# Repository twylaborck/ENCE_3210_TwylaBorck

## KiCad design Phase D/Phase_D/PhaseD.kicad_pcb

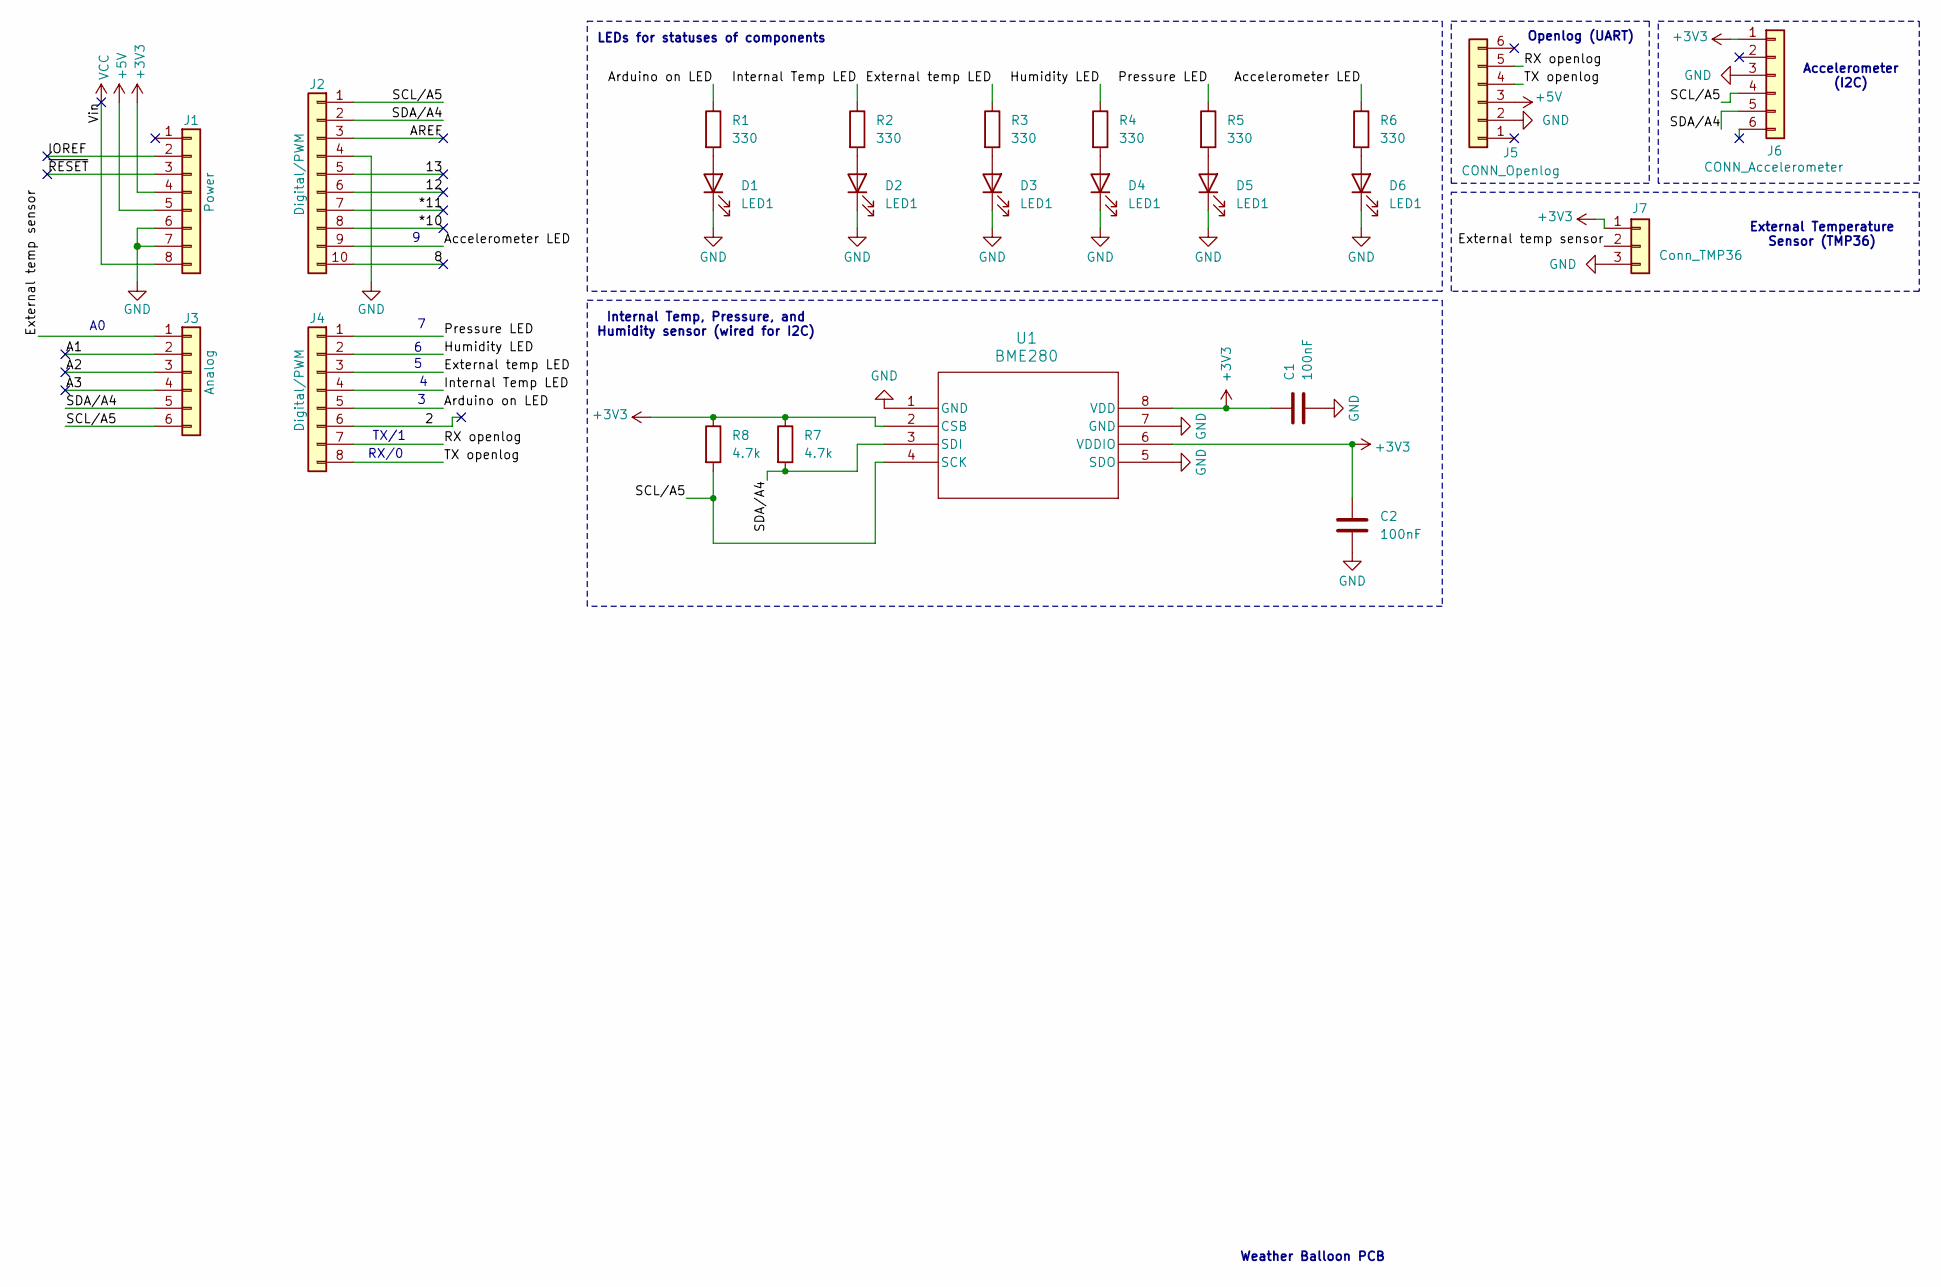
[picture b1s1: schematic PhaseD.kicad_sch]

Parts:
C1, C2: 100nF; C_Disc_D5.0mm_W2.5mm_P5.00mm
D1, D2, D3, D4, D5, D6: LED1; LED_D5.0mm
J1: Power; PinSocket_1x08_P2.54mm_Vertical
J2: Digital/PWM; PinSocket_1x10_P2.54mm_Vertical
J3: Analog; PinSocket_1x06_P2.54mm_Vertical
J4: Digital/PWM; PinSocket_1x08_P2.54mm_Vertical
J5: CONN_Openlog; PinHeader_1x06_P2.54mm_Vertical
J6: CONN_Accelerometer; PinHeader_1x06_P2.54mm_Vertical
J7: Conn_TMP36; PinHeader_1x03_P2.00mm_Vertical
R1, R2, R3, R4, R5, R6: 330; R_Axial_DIN0207_L6.3mm_D2.5mm_P10.16mm_Horizontal
R7, R8: 4.7k; R_Axial_DIN0207_L6.3mm_D2.5mm_P10.16mm_Horizontal
U1: BME280; DFN8_0p65_2p5SQ_BOS

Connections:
+3V3: C1.1, C2.1, J1.4, J6.1, J7.1, R7.1, R8.1, U1.2 (CSB), U1.6 (VDDIO), U1.8 (VDD)
+5V: J1.5, J5.3
/2: J4.6
/8: J2.10
/12: J2.6
/13: J2.5
/*10: J2.8
/*11: J2.7
/A1: J3.2
/A2: J3.3
/A3: J3.4
/AREF: J2.3
/Accelerometer LED: J2.9, R6.1
/Arduino on LED: J4.5, R1.1
/External temp LED: J4.3, R3.1
/External temp sensor: J3.1, J7.2
/Humidity LED: J4.2, R4.1
/IOREF: J1.2
/Internal Temp LED: J4.4, R2.1
/Pressure LED: J4.1, R5.1
/RX openlog: J4.7, J5.5
/SCL/A5: J2.1, J3.6, J6.4, R8.2, U1.4 (SCK)
/SDA/A4: J2.2, J3.5, J6.5, R7.2, U1.3 (SDI)
/TX openlog: J4.8, J5.4
/~RESET: J1.3
GND: C1.2, C2.2, D1.1 (K), D2.1 (K), D3.1 (K), D4.1 (K), D5.1 (K), D6.1 (K), J1.6, J1.7, J2.4, J5.2, J6.3, J7.3, U1.1 (GND), U1.5 (SDO), U1.7 (GND)
unnamed: D1.2 (A), R1.2
unnamed: D2.2 (A), R2.2
unnamed: D3.2 (A), R3.2
unnamed: D4.2 (A), R4.2
unnamed: D5.2 (A), R5.2
unnamed: D6.2 (A), R6.2
VCC: J1.8

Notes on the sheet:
Weather Balloon PCB
Internal Temp, Pressure, and Humidity sensor (wired for I2C)
TX/1
Openlog (UART)
RX/0
External Temperature Sensor (TMP36)
LEDs for statuses of components
Accelerometer (I2C)

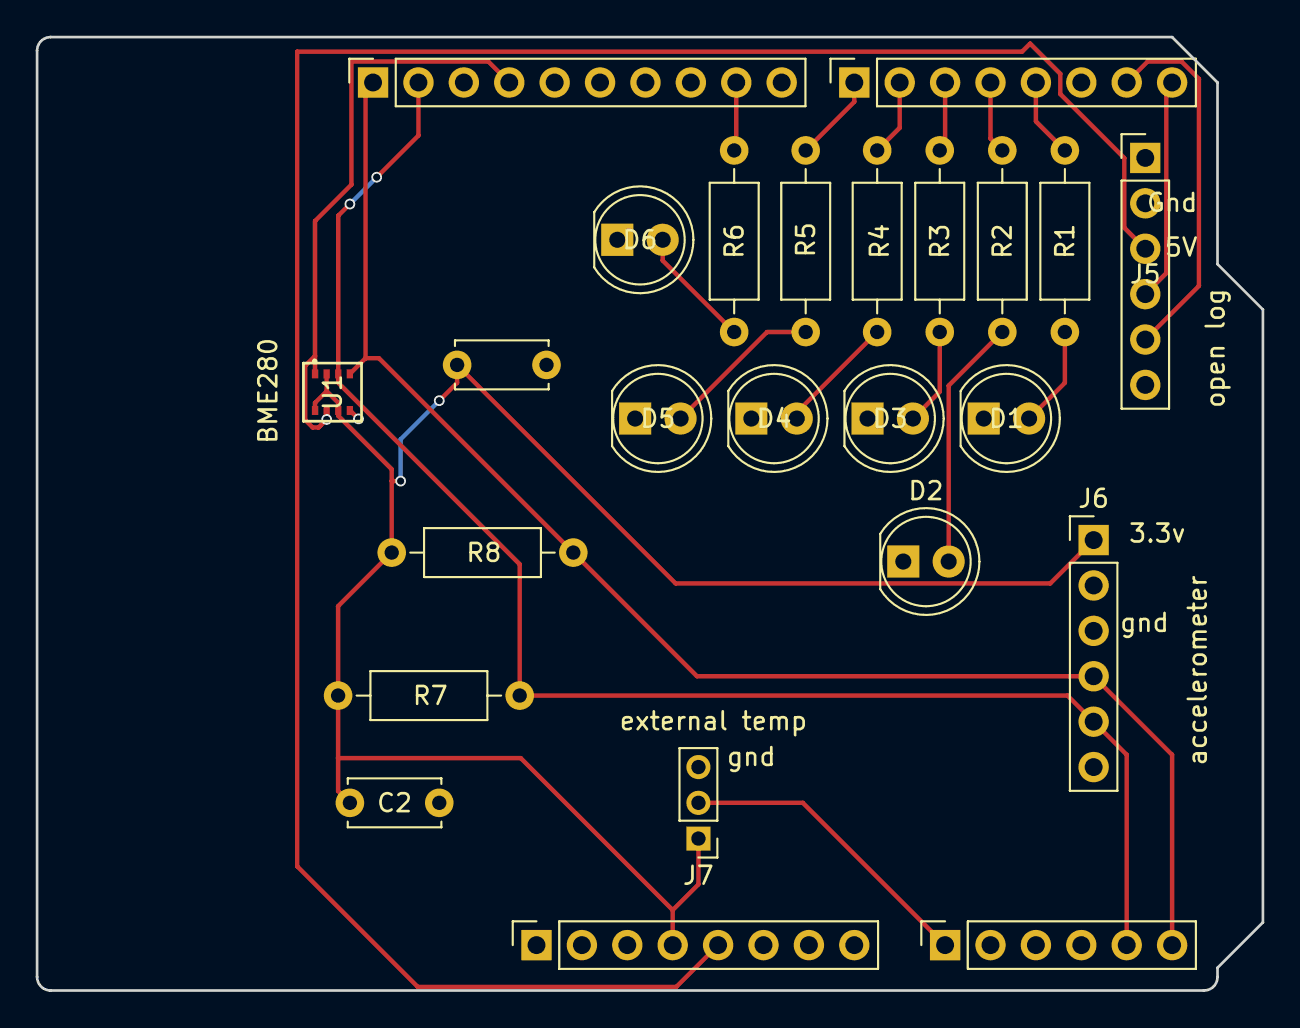
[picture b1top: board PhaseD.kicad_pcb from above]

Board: 2 copper layers, 68.6 x 53.3 mm, 24 parts (0 on the bottom side), 20 nets.

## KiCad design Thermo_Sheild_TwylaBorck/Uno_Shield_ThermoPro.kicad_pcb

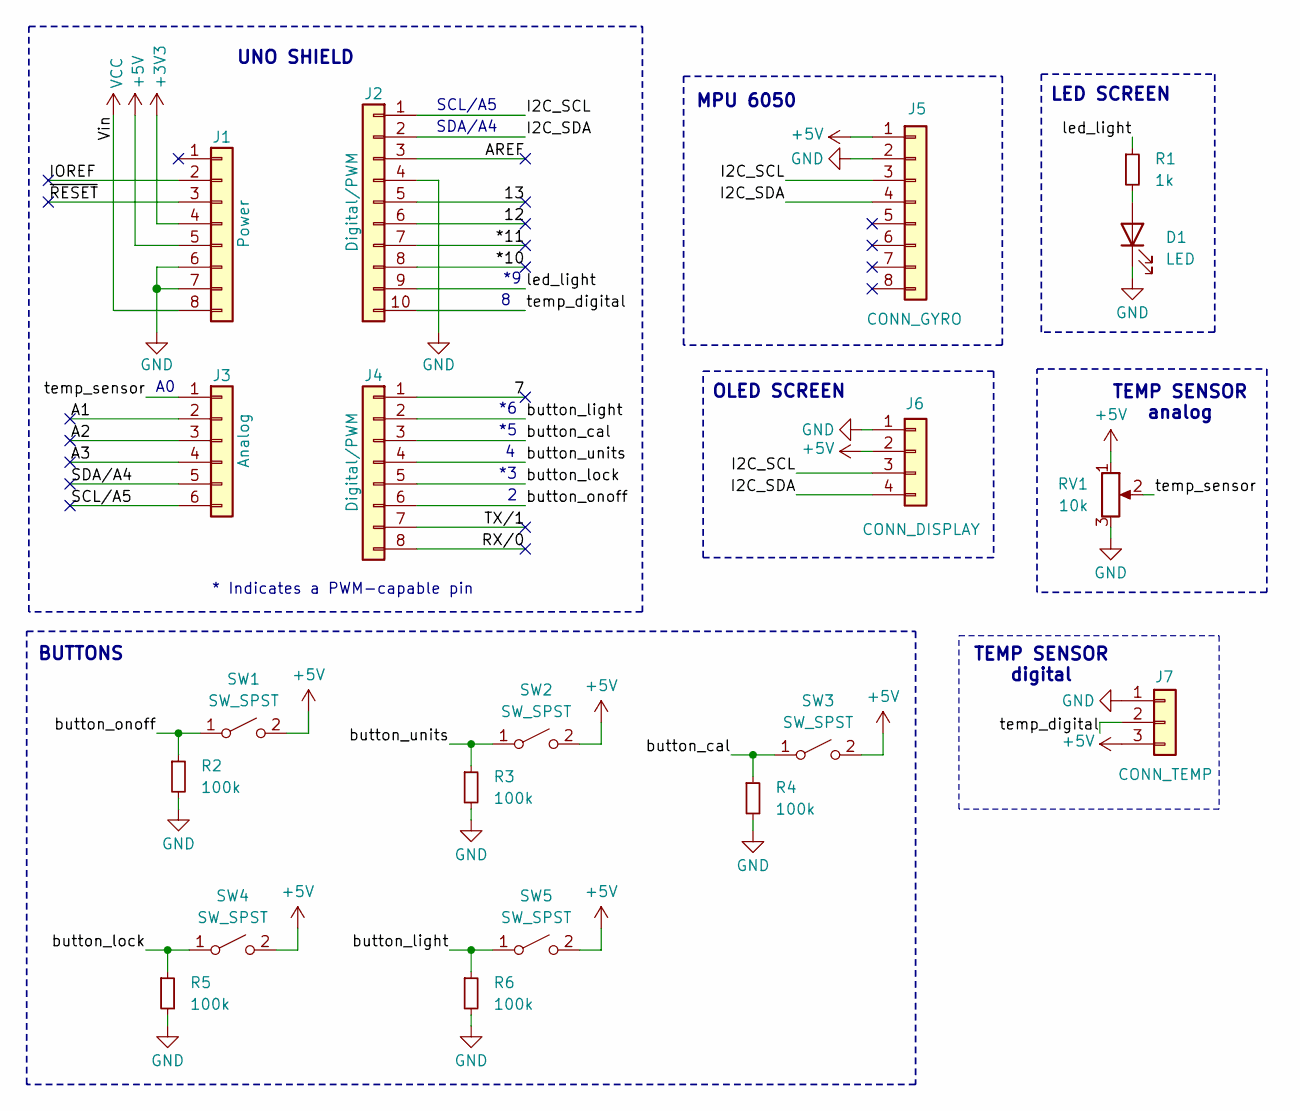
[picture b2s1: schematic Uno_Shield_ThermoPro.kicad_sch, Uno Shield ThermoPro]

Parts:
D1: LED; LED_D5.0mm
J1: Power; PinSocket_1x08_P2.54mm_Vertical
J2: Digital/PWM; PinSocket_1x10_P2.54mm_Vertical
J3: Analog; PinSocket_1x06_P2.54mm_Vertical
J4: Digital/PWM; PinSocket_1x08_P2.54mm_Vertical
J5: CONN_GYRO; PinSocket_1x08_P2.54mm_Vertical
J6: CONN_DISPLAY; PinSocket_1x04_P2.54mm_Vertical
J7: CONN_TEMP; JST_XH_B3B-XH-A_1x03_P2.50mm_Vertical
R1: 1k; R_Axial_DIN0207_L6.3mm_D2.5mm_P10.16mm_Horizontal
R2, R3, R4, R5, R6: 100k; R_Axial_DIN0207_L6.3mm_D2.5mm_P10.16mm_Horizontal
RV1: 10k; Potentiometer_Bourns_3386P_Vertical
SW1, SW2, SW3, SW4, SW5: SW_SPST; SW_PUSH_6mm

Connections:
+3V3: J1.4
+5V: J1.5, J5.1, J6.2, J7.3, RV1.1, SW1.2 (B), SW2.2 (B), SW3.2 (B), SW4.2 (B), SW5.2 (B)
/7: J4.1
/12: J2.6
/13: J2.5
/*10: J2.8
/*11: J2.7
/A1: J3.2
/A2: J3.3
/A3: J3.4
/AREF: J2.3
/I2C_SCL: J2.1, J5.3, J6.3
/I2C_SDA: J2.2, J5.4, J6.4
/IOREF: J1.2
/RX/0: J4.8
/SCL/A5: J3.6
/SDA/A4: J3.5
/TX/1: J4.7
/button_cal: J4.3, R4.1, SW3.1 (A)
/button_light: J4.2, R6.1, SW5.1 (A)
/button_lock: J4.5, R5.1, SW4.1 (A)
/button_onoff: J4.6, R2.1, SW1.1 (A)
/button_units: J4.4, R3.1, SW2.1 (A)
/led_light: J2.9, R1.1
/temp_digital: J2.10, J7.2
/temp_sensor: J3.1, RV1.2
/~RESET: J1.3
GND: D1.1 (K), J1.6, J1.7, J2.4, J5.2, J6.1, J7.1, R2.2, R3.2, R4.2, R5.2, R6.2, RV1.3
unnamed: D1.2 (A), R1.2
VCC: J1.8

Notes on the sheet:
OLED SCREEN
LED SCREEN
TEMP SENSOR analog
UNO SHIELD
MPU 6050
SCL/A5
SDA/A4
BUTTONS
* Indicates a PWM-capable pin
TEMP SENSOR digital

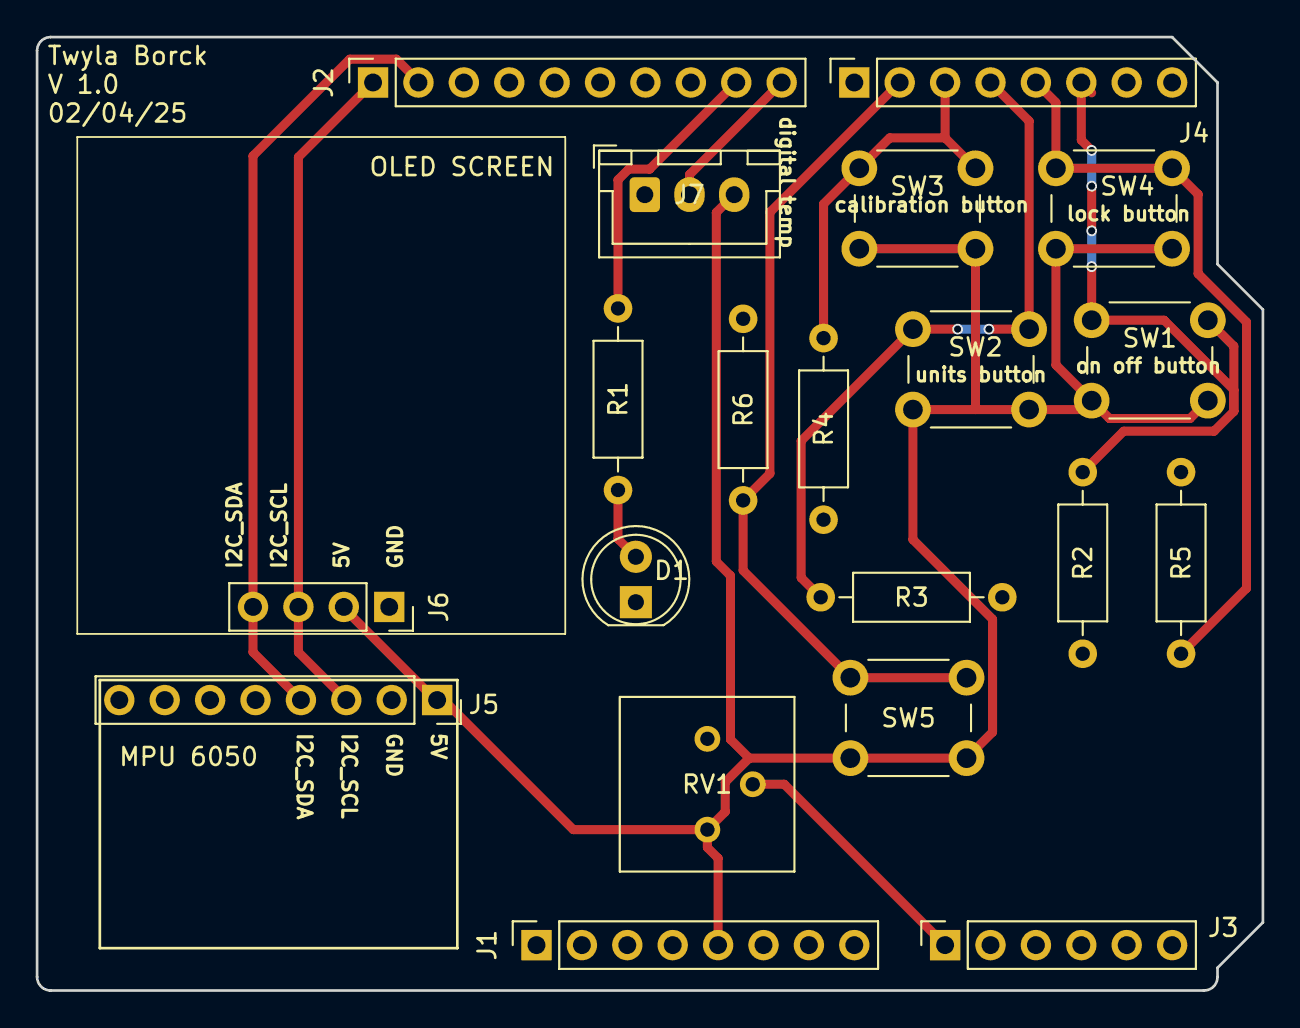
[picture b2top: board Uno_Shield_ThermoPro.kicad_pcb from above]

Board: 2 copper layers, 68.6 x 53.3 mm, 20 parts (0 on the bottom side), 13 nets.

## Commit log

2025-02-03 Create fp-info-cache
2025-02-04 added name to silkscreen
2025-02-26 thermo pro code
2025-03-03 lab 4 and added comment to thermoprocode
2025-03-12 not sure what this update is
2025-03-13 Phase D
2025-03-13 uploaded presentation and block diagrams for phase D
